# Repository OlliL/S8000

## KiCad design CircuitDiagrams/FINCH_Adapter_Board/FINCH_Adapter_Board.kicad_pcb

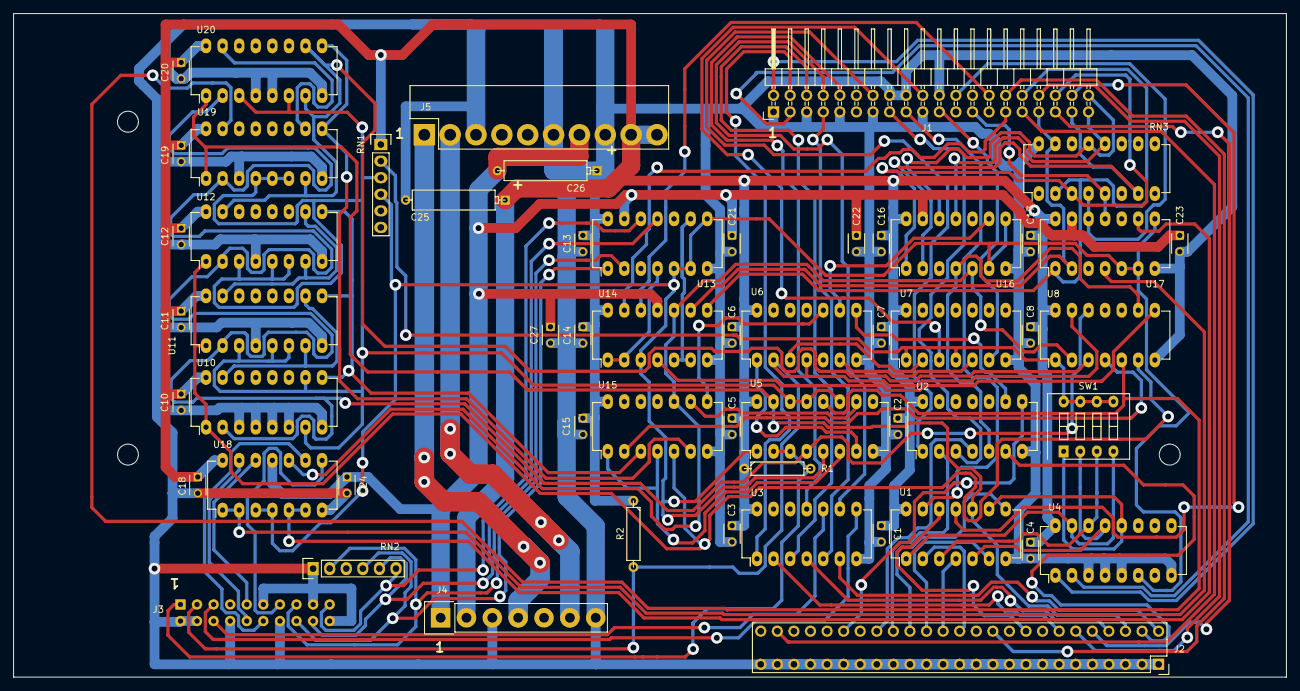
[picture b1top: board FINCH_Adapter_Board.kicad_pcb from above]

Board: 2 copper layers, 195.0 x 101.7 mm, 59 parts (1 on the bottom side), 89 nets.

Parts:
C1, C2, C3, C4, C5, C6, C7, C8, C10, C11, C12, C13, C14, C15, C16, C17, C18, C19, C20, C21, C22, C23, C24, C27: 100nF; C_Disc_D3_P2.5
C25, C26: 22uF; CP6
J1: CONN_02X20; Pin_Header_Angled_2x20
J2: CONN_02X25; Socket_Slot_2x25
J3: CONN_02X10; Conn_AMP-1-87456-6
J4: CONN_01X07; Conn_AMP-1-87270-5
J5: CONN_01X10; Conn_Molex-26-60-5100
MOUNT1, MOUNT2, MOUNT3: eMountingHole_3.2mm_M3; MountingHole_3.2mm_M3
R1, R2: 750; R4
RN1: 1k; Pin_Header_Straight_1x06
RN2: 56R; Pin_Header_Straight_1x06
RN3: 82R; DIP-16_W7.62mm_LongPads
SW1: DIPS_04; SW_DIP_x4_Slide
U1, U2: 7417; DIP-14_W7.62mm_LongPads
U3: 7416; DIP-14_W7.62mm_LongPads
U4: 74LS138; DIP-16_W7.62mm_LongPads
U5: 74LS109; DIP-16_W7.62mm_LongPads
U6: 74LS00; DIP-14_W7.62mm_LongPads
U7: 74LS125; DIP-14_W7.62mm_LongPads
U8: 74LS04; DIP-14_W7.62mm_LongPads
U10, U11, U12, U19, U20: 74LS163; DIP-16_W7.62mm_LongPads
U13, U16, U17: 75107; DIP-14_W7.62mm_LongPads
U14, U18: 75110; DIP-14_W7.62mm_LongPads
U15: 74LS08; DIP-14_W7.62mm_LongPads

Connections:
-5V: C21.1, C22.1, C23.1, C24.1, C26.2, C27.1, J4.1, J5.7, U13.13, U14.11, U16.13, U17.13, U18.11
/FINCH_Adapter_Board_02//CTRL_ATTN: J1.17, U1.13
/FINCH_Adapter_Board_02//CTRL_BI-DATA: J1.32, RN3.2, U14.8, U17.1
/FINCH_Adapter_Board_02//CTRL_CWD0: J1.14, U2.1
/FINCH_Adapter_Board_02//CTRL_CWD1: J1.15, U2.3
/FINCH_Adapter_Board_02//CTRL_INDEX: J1.20, U7.3
/FINCH_Adapter_Board_02//CTRL_MASTER_RESET: J1.38, U1.11
/FINCH_Adapter_Board_02//CTRL_READ-ENABLE: J1.36, RN3.3, U16.1
/FINCH_Adapter_Board_02//CTRL_SECTOR: J1.21, U7.6
/FINCH_Adapter_Board_02//CTRL_SYSTEMCLK: J1.29, U14.13
/FINCH_Adapter_Board_02//CTRL_UNITACK0: J1.30, J2.22
/FINCH_Adapter_Board_02//CTRL_UNITACK1: J1.31, J2.48
/FINCH_Adapter_Board_02//CTRL_UNITACK2: J1.34, J2.12
/FINCH_Adapter_Board_02//CTRL_UNITACK3: J1.35, J2.10
/FINCH_Adapter_Board_02//CTRL_WRITE-CLK: J1.24, RN3.4, U17.12
/FINCH_Adapter_Board_02//CTRL_WRITE_ENABLE: J1.39, RN3.12, U16.11
/FINCH_Adapter_Board_02/CTRL_BI-DATA: J1.33, RN3.15, U14.9, U17.2
/FINCH_Adapter_Board_02/CTRL_CB0: J1.2, U4.1
/FINCH_Adapter_Board_02/CTRL_CB1: J1.3, U4.2
/FINCH_Adapter_Board_02/CTRL_CB2: J1.4, U3.1
/FINCH_Adapter_Board_02/CTRL_CB3: J1.6, U3.3
/FINCH_Adapter_Board_02/CTRL_CB4: J1.7, U3.5
/FINCH_Adapter_Board_02/CTRL_CB5: J1.8, U3.9
/FINCH_Adapter_Board_02/CTRL_CB6: J1.10, U3.11
/FINCH_Adapter_Board_02/CTRL_READ_ENABLE: J1.37, RN3.7, U16.2
/FINCH_Adapter_Board_02/CTRL_SYSTEMCLK: J1.28, U14.12
/FINCH_Adapter_Board_02/CTRL_WRITE-CLK: J1.25, RN3.5, U17.11
/FINCH_Adapter_Board_02/CTRL_WRITE_ENABLE: J1.40, RN3.13, U16.12
/FINCH_Adapter_Board_02/DRV_CMD_DIRECTION: J2.36, U2.4
/FINCH_Adapter_Board_02/DRV_CMD_DRIVE_SELECT_1: J2.26, U1.2
/FINCH_Adapter_Board_02/DRV_CMD_DRIVE_SELECT_2: J2.28, U1.4
/FINCH_Adapter_Board_02/DRV_CMD_DRIVE_SELECT_3: J2.30, U1.6
/FINCH_Adapter_Board_02/DRV_CMD_DRIVE_SELECT_4: J2.32, U1.8
/FINCH_Adapter_Board_02/DRV_CMD_HEAD_SELECT_2_0: J2.14, U3.2
/FINCH_Adapter_Board_02/DRV_CMD_HEAD_SELECT_2_1: J2.8, U3.4
/FINCH_Adapter_Board_02/DRV_CMD_READ_ENABLE: J2.4, U2.6
/FINCH_Adapter_Board_02/DRV_CMD_RESERVED_1: J2.2, U3.6
/FINCH_Adapter_Board_02/DRV_CMD_RETURN_TO_ZERO: J2.18, U1.12
/FINCH_Adapter_Board_02/DRV_CMD_STEP: J2.34, U2.2
/FINCH_Adapter_Board_02/DRV_DATA_EARLY_DS_ENABLE: J3.5, U3.8
/FINCH_Adapter_Board_02/DRV_DATA_LATE_DS_ENABLE: J3.6, U3.10
/FINCH_Adapter_Board_02/DRV_DATA_READ_DATA_+: J3.18, RN2.5, U13.11
/FINCH_Adapter_Board_02/DRV_DATA_READ_DATA_-: J3.19, RN2.6, U13.12
/FINCH_Adapter_Board_02/DRV_DATA_SERVO_READ_CLK_+: J3.15, RN2.2, U13.2
/FINCH_Adapter_Board_02/DRV_DATA_SERVO_READ_CLK_-: J3.16, RN2.4, U13.1
/FINCH_Adapter_Board_02/DRV_DATA_WRITE_CLK_+: J3.12, U18.9
/FINCH_Adapter_Board_02/DRV_DATA_WRITE_CLK_-: J3.13, U18.8
/FINCH_Adapter_Board_02/DRV_DATA_WRITE_DATA_+: J3.9, U18.12
/FINCH_Adapter_Board_02/DRV_DATA_WRITE_DATA_-: J3.10, U18.13
/INDEX: U6.3, U7.2
/MASTER_RESET: J2.6, U1.10, U5.15, U19.1, U20.1
/SECTOR: U6.6, U7.5
DRIVE_SELECT: U8.2, U14.10, U15.10, U16.5, U18.10
DRV_CMD_WRITE_ENABLE: J2.40, U2.8
DRV_DATA_BYTE_CLOCK: J3.3, R2.2, U6.2, U6.4, U8.13
DRV_DATA_INDEX: J3.1, R1.2, U5.2, U5.3
GND: C1.2, C2.2, C3.2, C4.2, C5.2, C6.2, C7.2, C8.2, C10.2, C11.2, C12.2, C13.2, C14.2, C15.2, C16.2, C17.2, C18.2, C19.2, C20.2, C21.2, C22.2, C23.2, C24.2, C25.2, C26.1, C27.2, J1.1, J1.5, J1.9, J1.13, J1.16, J1.18, J1.19, J1.22, J2.1, J2.3, J2.5, J2.7, J2.9, J2.11, J2.13, J2.15, J2.17, J2.19, J2.21, J2.23, J2.25, J2.27, J2.29, J2.31, J2.33, J2.35, J2.37, J2.39, J2.41, J2.43, J2.45, J2.47, J2.49, J3.2, J3.4, J3.8, J3.11, J3.14, J3.17, J3.20, J4.3, J4.7, J5.3, J5.6, J5.8, RN2.1, RN3.16, U1.7, U2.7, U3.7, U4.3, U4.4, U4.5, U4.8, U5.8, U6.7, U7.7, U8.7, U10.3, U10.4, U10.5, U10.6, U10.8, U11.4, U11.8, U12.4, U12.8, U13.7, U14.7, U15.7, U16.7, U17.7, U18.7, U19.3, U19.8, U20.4, U20.5, U20.8
HIGH_2: RN1.3, U5.11, U5.13, U5.14, U10.7, U10.10, U11.3, U11.5, U11.6, U12.3, U12.5, U12.6, U19.4, U19.5, U19.6, U20.3, U20.6
HIGH_3: RN1.4, U4.6, U5.1, U5.5, U13.5, U13.6, U13.8, U14.3, U16.6, U16.8, U17.5, U17.6, U17.8, U18.3, U18.4
unnamed: J4.4, J5.1
unnamed: J4.6, J5.2
unnamed: RN1.2, SW1.5, SW1.6, SW1.7, SW1.8, U7.1, U7.4, U8.1
unnamed: SW1.1, U1.9, U4.12
unnamed: SW1.2, U1.5, U4.13
unnamed: SW1.3, U1.3, U4.14
unnamed: SW1.4, U1.1, U4.15
unnamed: U2.9, U6.8
unnamed: U5.7, U6.1
unnamed: U8.6, U10.1, U11.1, U12.1, U15.5
unnamed: U5.4, U8.12, U10.2, U11.2, U12.2, U19.2, U20.2
unnamed: U10.9, U11.9, U12.9, U15.3
unnamed: U10.15, U11.7, U11.10
unnamed: U11.15, U12.7, U12.10
unnamed: U6.5, U8.3, U12.15, U19.7, U20.7, U20.10
unnamed: U13.4, U14.1, U14.2
unnamed: U13.9, U14.5, U14.6
unnamed: U8.8, U14.4
unnamed: U5.6, U15.1, U15.4
unnamed: U8.4, U15.2
unnamed: U15.6, U19.9, U20.9
unnamed: U6.10, U15.8
unnamed: U5.10, U15.9
unnamed: U2.5, U8.9, U16.4
unnamed: U17.4, U18.1, U18.2
unnamed: U17.9, U18.5, U18.6
unnamed: U19.10, U20.15
unnamed: U5.12, U8.5, U19.15
VCC: C1.1, C2.1, C3.1, C4.1, C5.1, C6.1, C7.1, C8.1, C10.1, C11.1, C12.1, C13.1, C14.1, C15.1, C16.1, C17.1, C18.1, C19.1, C20.1, C25.1, J4.2, J5.9, J5.10, R1.1, R2.1, RN1.1, U1.14, U2.14, U3.14, U4.16, U5.16, U6.14, U7.14, U8.14, U10.16, U11.16, U12.16, U13.14, U14.14, U15.14, U16.14, U17.14, U18.14, U19.16, U20.16
WRITE_ENABLE: U6.9, U16.9

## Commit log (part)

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2016-01-11 Zilog System 8000 CPU Firmware version 2.2
2016-01-12 begin 1.2
2016-01-13 more work
2016-01-14 more work on 1.2
2016-01-15 fix some hardcoded RAM and Firmware addresses
2016-01-15 make version 1.2 100% compatible to the original firmware
2016-01-15 fix modes
2016-01-15 remove ADDR comments
2016-01-15 make more equal to 2.2 for better comparision
2016-01-15 make SIO handling better by decrypting the control codes
2016-01-15 remove spaces and tabs in empty lines
2016-01-18 comment WDC test routines
2016-01-18 remove spaces/tabs at lineend
2016-01-18 more comments
2016-01-21 disassembled md driver
2016-01-21 recorded WDC Selftest Captures
2016-01-21 zd driver
2016-07-05 begin work on the FINCH Adapter Board Circuit
2016-07-05 add signals
2016-07-09 todays work
2016-07-14 more work in cleanup and some fixes
2016-07-15 cleanup schematic
2016-07-16 fix some errors
2016-07-18 fix small errors, start PCB
2016-07-19 add new footprints
2016-07-19 add lib table
2016-07-21 todays work I
2016-07-21 todays work II
2016-07-22 todays work with bottom restriction
2016-07-25 todays work - now everything is connected and DRC is successful
2016-07-26 change 24V power supply a bit
2016-07-27 fix some stuff
2016-08-04 24V generation of the Disk/Tape PSU
2016-08-04 add partial Motor Board schematic
2016-08-07 new stuff
2016-08-08 more work on MainBoard
